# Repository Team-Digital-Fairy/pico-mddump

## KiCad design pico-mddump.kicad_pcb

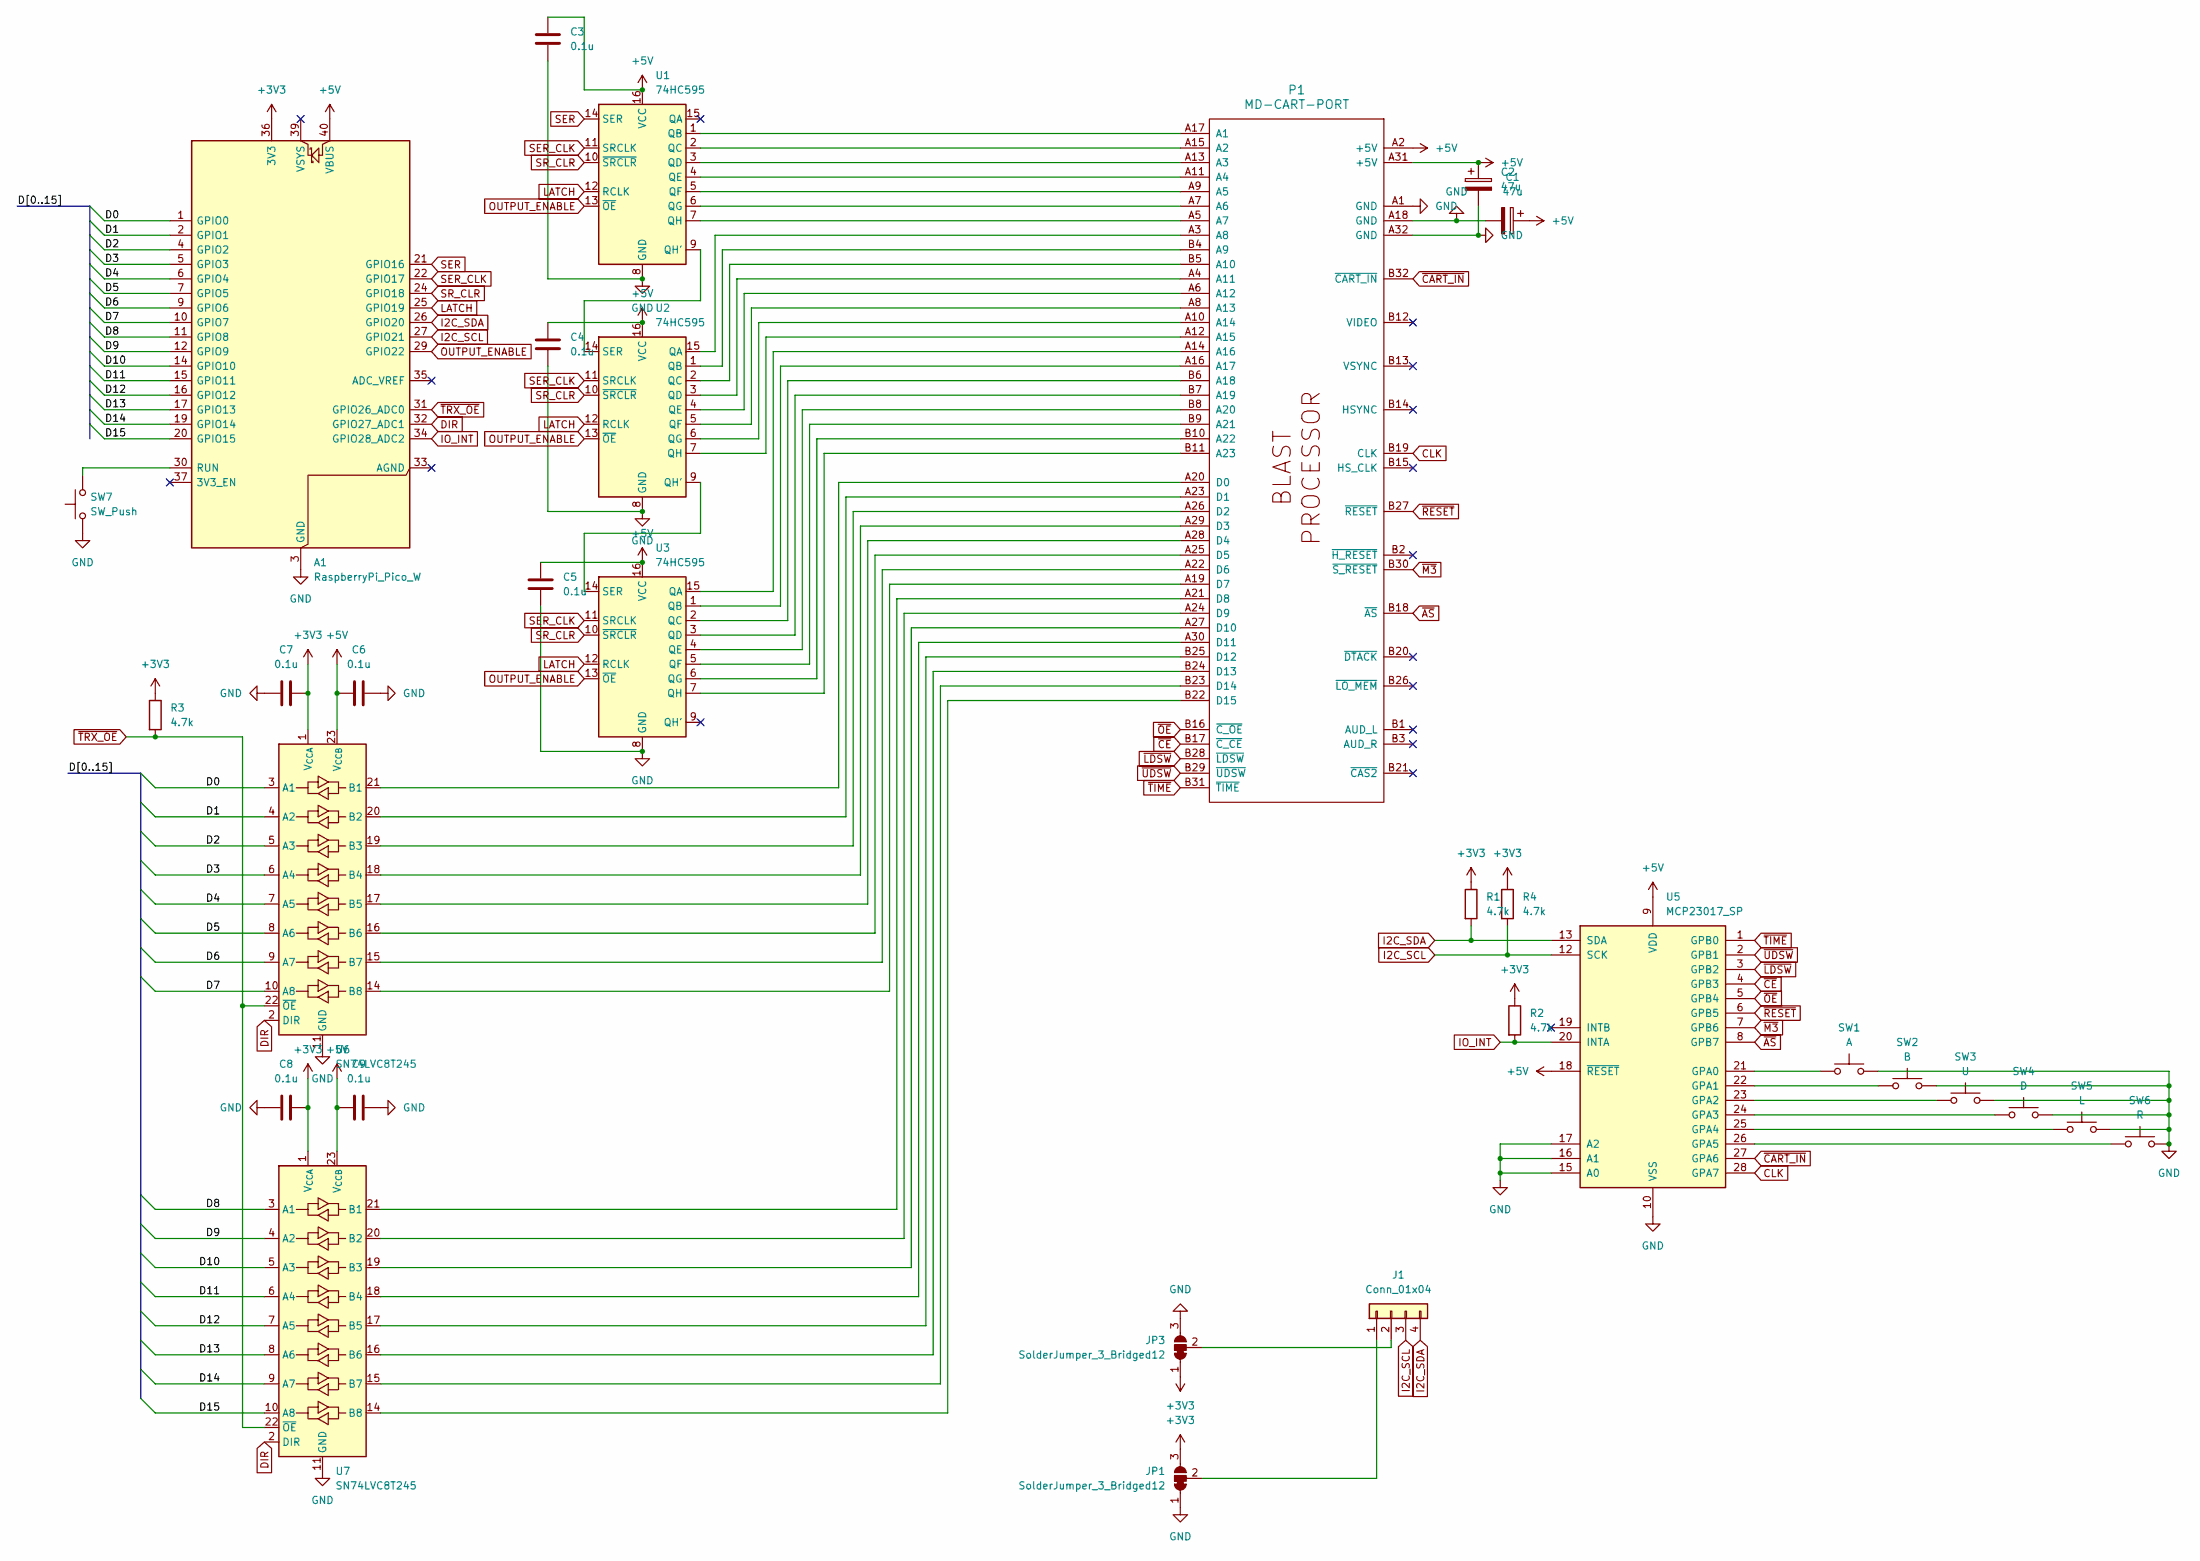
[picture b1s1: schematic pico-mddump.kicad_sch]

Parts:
A1: RaspberryPi_Pico_W; RaspberryPi_Pico_Common
C1, C2: 47u; CP_Radial_D5.0mm_P2.50mm
C3, C4, C5, C6, C7, C8, C9: 0.1u; C_Disc_D5.1mm_W3.2mm_P5.00mm
J1: Conn_01x04; PinSocket_1x04_P2.54mm_Vertical
JP1, JP3: SolderJumper_3_Bridged12; SolderJumper-3_P1.3mm_Bridged12_RoundedPad1.0x1.5mm
P1: MD-CART-PORT; GEN_CART_PORT
R1, R2, R3, R4: 4.7k; R_Axial_DIN0207_L6.3mm_D2.5mm_P10.16mm_Horizontal
SW1: A; SW_PUSH_6mm
SW2: B; SW_PUSH_6mm
SW3: U; SW_PUSH_6mm
SW4: D; SW_PUSH_6mm
SW5: L; SW_PUSH_6mm
SW6: R; SW_PUSH_6mm
SW7: SW_Push; SW_PUSH_6mm
U1, U2, U3: 74HC595; DIP-16_W7.62mm
U5: MCP23017_SP; DIP-28_W7.62mm
U6, U7: SN74LVC8T245; TSSOP-24_4.4x7.8mm_P0.65mm

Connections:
+3V3: A1.36 (3V3), C7.2, C8.2, JP1.3 (B), JP3.1 (A), R1.1, R2.1, R3.1, R4.1, U6.1 (V_{CCA}), U7.1 (V_{CCA})
+5V: A1.40 (VBUS), C1.1, C2.1, C3.1, C4.1, C5.1, C6.1, C9.1, P1.A2 (+5V), P1.A31 (+5V), U1.16 (VCC), U2.16 (VCC), U3.16 (VCC), U5.9 (VDD), U5.18 (~RESET), U6.23 (V_{CCB}), U6.24 (V_{CCB}), U7.23 (V_{CCB}), U7.24 (V_{CCB})
/D0: A1.1 (GPIO0), U6.3 (A1)
/D1: A1.2 (GPIO1), U6.4 (A2)
/D2: A1.4 (GPIO2), U6.5 (A3)
/D3: A1.5 (GPIO3), U6.6 (A4)
/D4: A1.6 (GPIO4), U6.7 (A5)
/D5: A1.7 (GPIO5), U6.8 (A6)
/D6: A1.9 (GPIO6), U6.9 (A7)
/D7: A1.10 (GPIO7), U6.10 (A8)
/D8: A1.11 (GPIO8), U7.3 (A1)
/D9: A1.12 (GPIO9), U7.4 (A2)
/D10: A1.14 (GPIO10), U7.5 (A3)
/D11: A1.15 (GPIO11), U7.6 (A4)
/D12: A1.16 (GPIO12), U7.7 (A5)
/D13: A1.17 (GPIO13), U7.8 (A6)
/D14: A1.19 (GPIO14), U7.9 (A7)
/D15: A1.20 (GPIO15), U7.10 (A8)
CLK: P1.B19 (CLK), U5.28 (GPA7)
DIR: A1.32 (GPIO27_ADC1), U6.2 (DIR), U7.2 (DIR)
GND: A1.3 (GND), A1.8 (GND), A1.13 (GND), A1.18 (GND), A1.23 (GND), A1.28 (GND), A1.38 (GND), C1.2, C2.2, C3.2, C4.2, C5.2, C6.2, C7.1, C8.1, C9.2, JP1.1 (A), JP3.3 (B), P1.A1 (GND), P1.A18 (GND), P1.A32 (GND), SW1.2, SW2.2, SW3.2, SW4.2, SW5.2, SW6.2, SW7.1, U1.8 (GND), U2.8 (GND), U3.8 (GND), U5.10 (VSS), U5.15 (A0), U5.16 (A1), U5.17 (A2), U6.11 (GND), U6.12 (GND), U6.13 (GND), U7.11 (GND), U7.12 (GND), U7.13 (GND)
I2C_SCL: A1.27 (GPIO21), J1.3, R4.2, U5.12 (SCK)
I2C_SDA: A1.26 (GPIO20), J1.4, R1.2, U5.13 (SDA)
IO_INT: A1.34 (GPIO28_ADC2), R2.2, U5.20 (INTA)
LATCH: A1.25 (GPIO19), U1.12 (RCLK), U2.12 (RCLK), U3.12 (RCLK)
unnamed: A1.30 (RUN), SW7.2
unnamed: J1.1, JP1.2 (C)
unnamed: J1.2, JP3.2 (C)
unnamed: P1.A17 (A1), U1.1 (QB)
unnamed: P1.A15 (A2), U1.2 (QC)
unnamed: P1.A13 (A3), U1.3 (QD)
unnamed: P1.A11 (A4), U1.4 (QE)
unnamed: P1.A9 (A5), U1.5 (QF)
unnamed: P1.A7 (A6), U1.6 (QG)
unnamed: P1.A5 (A7), U1.7 (QH)
unnamed: P1.A3 (A8), U2.15 (QA)
unnamed: P1.B4 (A9), U2.1 (QB)
unnamed: P1.B5 (A10), U2.2 (QC)
unnamed: P1.A4 (A11), U2.3 (QD)
unnamed: P1.A6 (A12), U2.4 (QE)
unnamed: P1.A8 (A13), U2.5 (QF)
unnamed: P1.A10 (A14), U2.6 (QG)
unnamed: P1.A12 (A15), U2.7 (QH)
unnamed: P1.A14 (A16), U3.15 (QA)
unnamed: P1.A16 (A17), U3.1 (QB)
unnamed: P1.B6 (A18), U3.2 (QC)
unnamed: P1.B7 (A19), U3.3 (QD)
unnamed: P1.B8 (A20), U3.4 (QE)
unnamed: P1.B9 (A21), U3.5 (QF)
unnamed: P1.B10 (A22), U3.6 (QG)
unnamed: P1.B11 (A23), U3.7 (QH)
unnamed: P1.A20 (D0), U6.21 (B1)
unnamed: P1.A23 (D1), U6.20 (B2)
unnamed: P1.A26 (D2), U6.19 (B3)
unnamed: P1.A29 (D3), U6.18 (B4)
unnamed: P1.A28 (D4), U6.17 (B5)
unnamed: P1.A25 (D5), U6.16 (B6)
unnamed: P1.A22 (D6), U6.15 (B7)
unnamed: P1.A19 (D7), U6.14 (B8)
unnamed: P1.A21 (D8), U7.21 (B1)
unnamed: P1.A24 (D9), U7.20 (B2)
unnamed: P1.A27 (D10), U7.19 (B3)
unnamed: P1.A30 (D11), U7.18 (B4)
unnamed: P1.B25 (D12), U7.17 (B5)
unnamed: P1.B24 (D13), U7.16 (B6)
unnamed: P1.B23 (D14), U7.15 (B7)
unnamed: P1.B22 (D15), U7.14 (B8)
unnamed: U1.9 (QH'), U2.14 (SER)
unnamed: U2.9 (QH'), U3.14 (SER)
unnamed: SW1.1, U5.21 (GPA0)
unnamed: SW2.1, U5.22 (GPA1)
unnamed: SW3.1, U5.23 (GPA2)
unnamed: SW4.1, U5.24 (GPA3)
unnamed: SW5.1, U5.25 (GPA4)
unnamed: SW6.1, U5.26 (GPA5)
OUTPUT_ENABLE: A1.29 (GPIO22), U1.13 (~OE), U2.13 (~OE), U3.13 (~OE)
SER: A1.21 (GPIO16), U1.14 (SER)
SER_CLK: A1.22 (GPIO17), U1.11 (SRCLK), U2.11 (SRCLK), U3.11 (SRCLK)
SR_CLR: A1.24 (GPIO18), U1.10 (~SRCLR), U2.10 (~SRCLR), U3.10 (~SRCLR)
~AS: P1.B18 (~AS), U5.8 (GPB7)
~CART_IN: P1.B32 (~CART_IN), U5.27 (GPA6)
~CE: P1.B17 (~C_CE), U5.4 (GPB3)
~LDSW: P1.B28 (~LDSW), U5.3 (GPB2)
~M3: P1.B30 (~S_RESET), U5.7 (GPB6)
~OE: P1.B16 (~C_OE), U5.5 (GPB4)
~RESET: P1.B27 (~RESET), U5.6 (GPB5)
~TIME: P1.B31 (~TIME), U5.1 (GPB0)
~TRX_OE: A1.31 (GPIO26_ADC0), R3.2, U6.22 (~OE), U7.22 (~OE)
~UDSW: P1.B29 (~UDSW), U5.2 (GPB1)

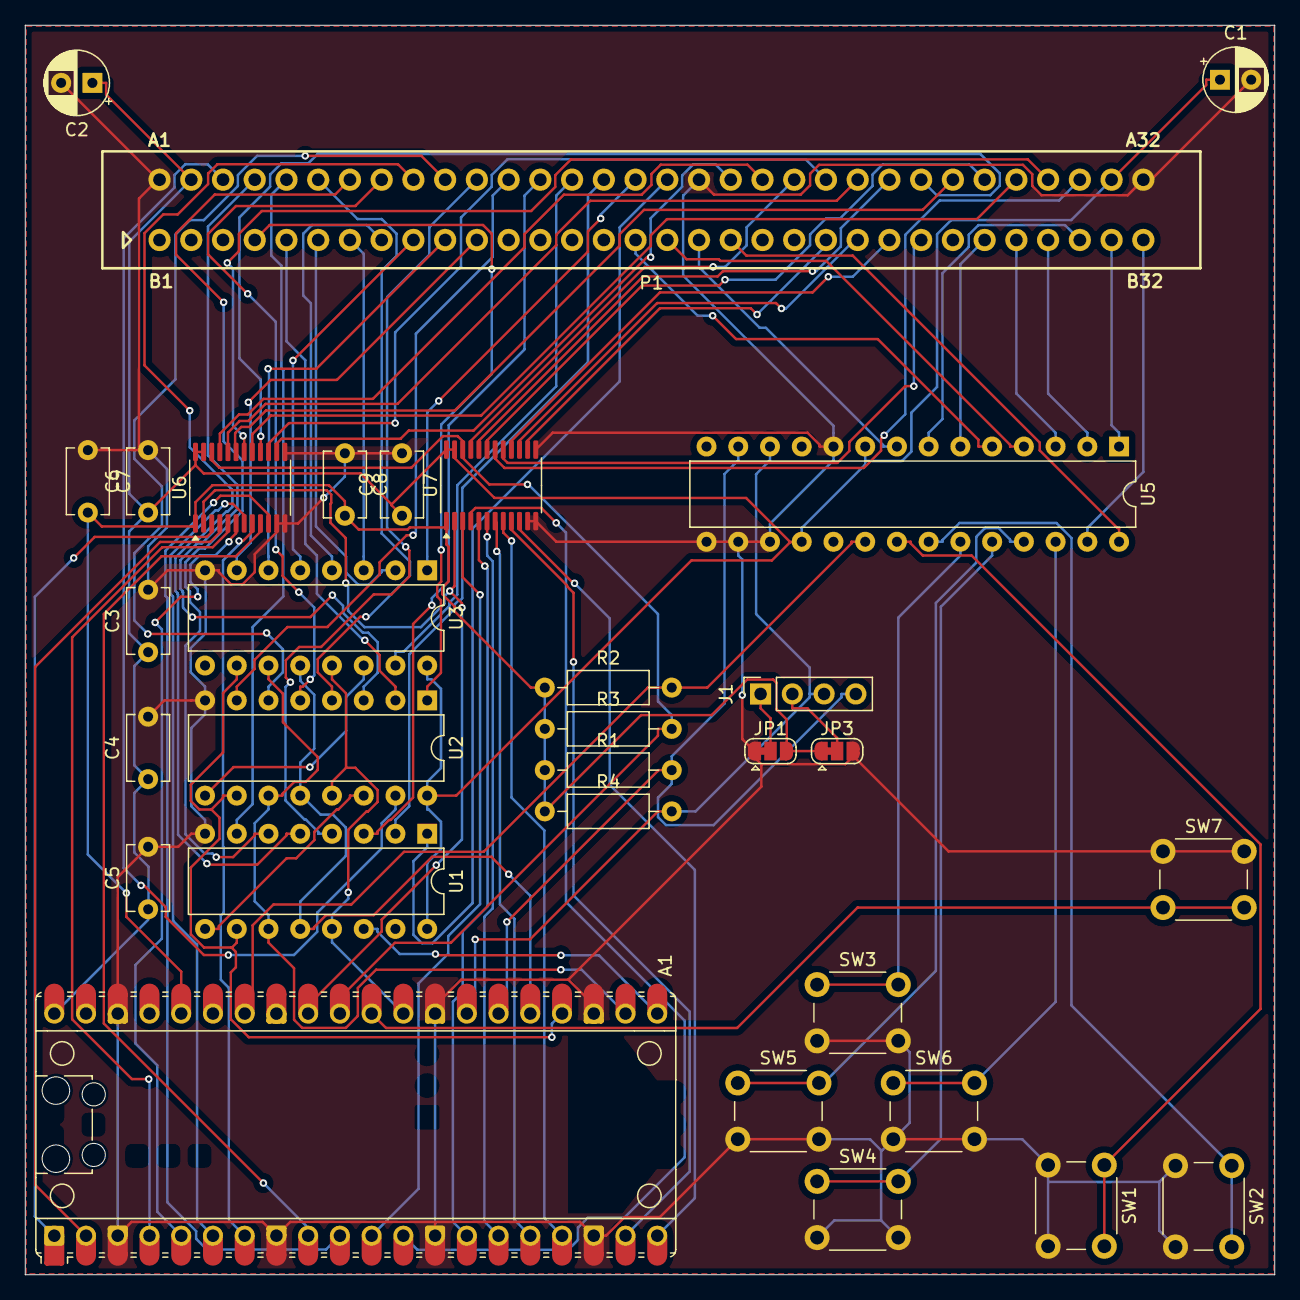
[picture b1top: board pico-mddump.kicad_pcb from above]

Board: 2 copper layers, 100.0 x 100.0 mm, 31 parts (0 on the bottom side), 89 nets.

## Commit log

2024-11-06 Init
